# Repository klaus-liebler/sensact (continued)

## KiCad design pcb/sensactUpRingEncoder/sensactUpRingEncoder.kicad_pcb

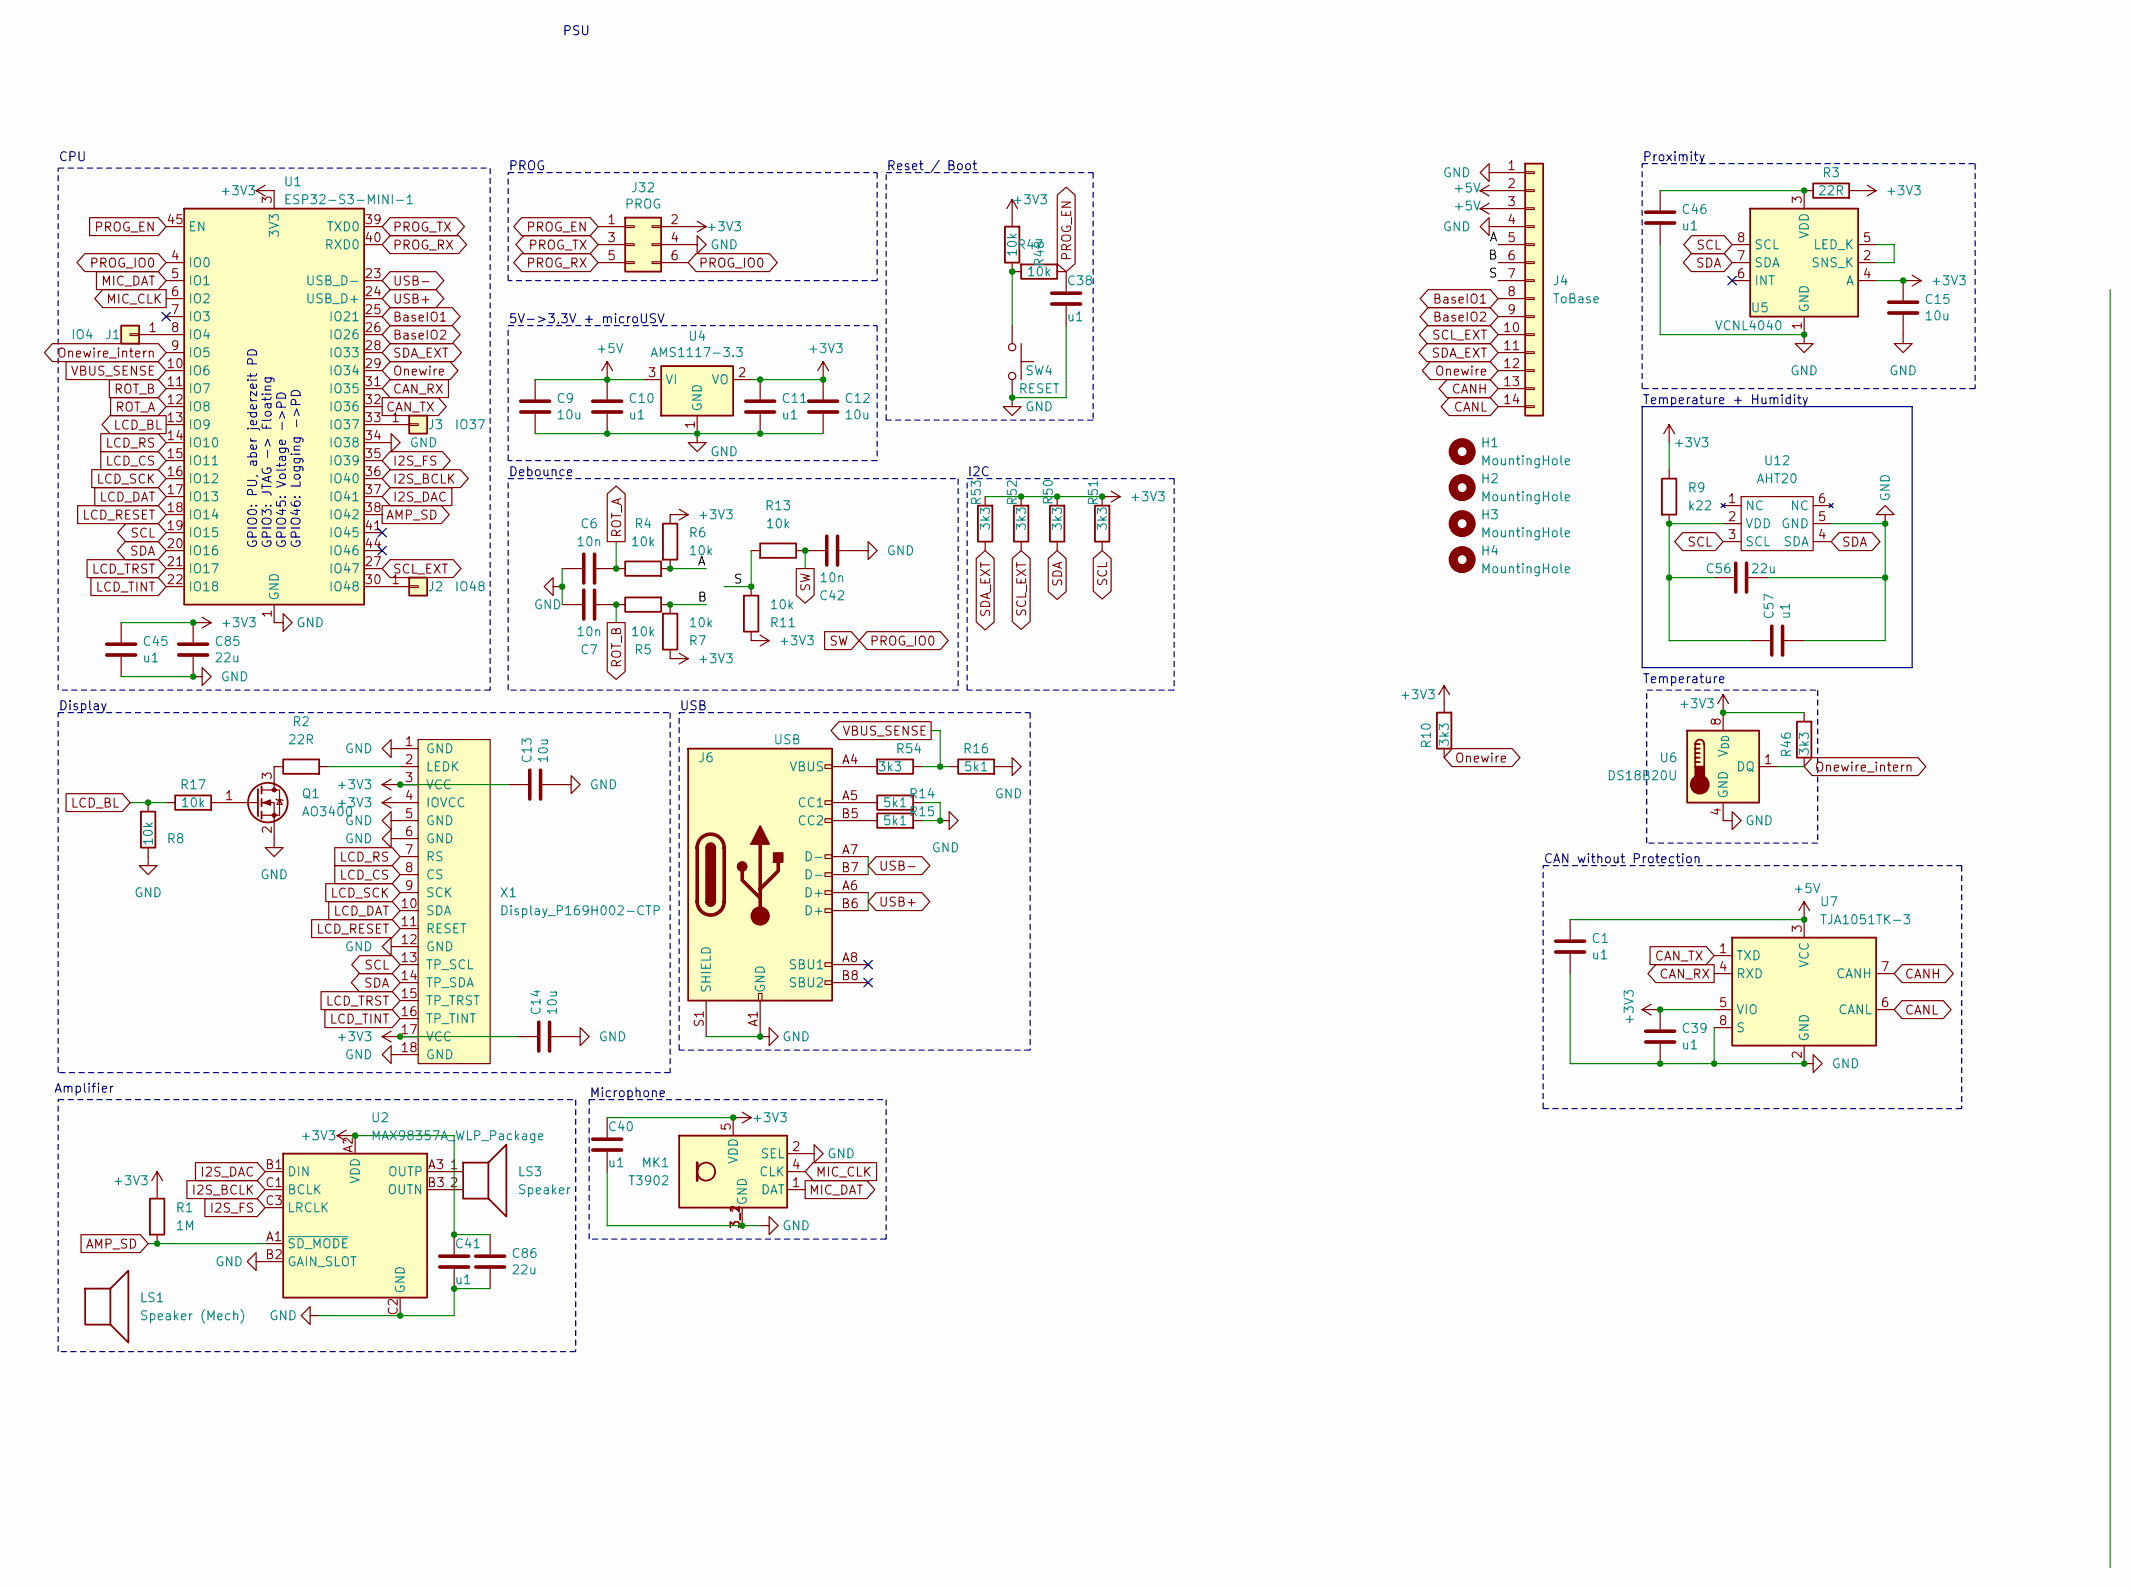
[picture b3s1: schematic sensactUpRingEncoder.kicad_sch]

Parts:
C1, C10, C11, C38, C39, C40, C41, C45, C46: u1; C_0201_0603Metric
C6, C7, C42: 10n; C_0201_0603Metric
C9, C12, C13, C14, C15: 10u; C_0402_1005Metric
C56, C85, C86: 22u; C_0603_1608Metric; MPN CL10A226MP8NUNE
C57: u1; C_0201_0603Metric; MPN GRM033R61A104KE15D
H1, H2, H3, H4: MountingHole; MountingHole_2.2mm_M2_DIN965
J1: IO4; TestPoint_THTPad_D1.0mm_Drill0.5mm
J2: IO48; TestPoint_THTPad_D1.5mm_Drill0.7mm
J3: IO37; TestPoint_THTPad_D1.5mm_Drill0.7mm
J4: ToBase; Hirose_FH12-14S-0.5SH_1x14-1MP_P0.50mm_Horizontal
J6: USB; USB_C_Receptacle_HRO_TYPE-C-31-M-12
J32: PROG; PinHeader_2x03_P1.27mm_Vertical_SMD
LS1: Speaker (Mech); SPEAKER_2415
LS3: Speaker; PinHeader_1x02_P1.27mm_Vertical
MK1: T3902; MIC_T3902
Q1: AO3400; SOT-23_smaller
R1: 1M; R_0805_2012Metric_Pad1.20x1.40mm_HandSolder
R2, R3: 22R; R_0805_2012Metric
R4, R5, R6, R7, R8, R11, R13, R17, R47, R48: 10k; R_0201_0603Metric
R9: k22; R_0805_2012Metric_Pad1.20x1.40mm_HandSolder; MPN 0402WGF2200TCE
R10, R46: 3k3; R_0402_1005Metric
R14, R15, R16: 5k1; R_0402_1005Metric
R50, R51, R52, R53, R54: 3k3; R_0402_1005Metric; MPN 0402WGF3301TCE
SW4: RESET; SW_Push_SPST_NO_4x3x2_handsolder
U1: ESP32-S3-MINI-1
U2: MAX98357A_WLP_Package; Maxim_WLP-9_1.595x1.415_Layout3x3_P0.4mm_Ball0.27mm_Pad0.25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
U4: AMS1117-3.3; SOT-223-3_TabPin2
U5: VCNL4040; VCNL4040_handsolder
U6: DS18B20U; MSOP-8_3x3mm_P0.65mm_handsolder
U7: TJA1051TK-3; HVSON-8-1EP_3x3mm_P0.65mm_EP1.6x2.4mm
U12: AHT20; AHT21; MPN AHT20
X1: Display_P169H002-CTP

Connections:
+3V3: C11.1, C12.1, C13.1, C14.1, C15.1, C39.1, C40.1, C41.1, C45.1, C85.1, C86.1, J32.2, MK1.5 (VDD), R1.1, R3.2, R6.1, R7.1, R9.1, R10.2, R11.1, R46.2, R47.2, R50.2, R51.2, R52.2, R53.2, U1.3 (3V3), U2.A2 (VDD), U4.2 (VO), U5.4 (A), U6.8 (V_{DD}), U7.5 (VIO), X1.3 (VCC), X1.4 (IOVCC), X1.17 (VCC)
+5V: C1.1, C9.1, C10.1, J4.2, J4.3, U4.3 (VI), U7.3 (VCC)
/A: J4.5, R4.2, R6.2
/B: J4.6, R5.2, R7.2
/S: J4.7, R11.2, R13.2
AMP_SD: R1.2, U1.38 (IO42), U2.A1 (~SD_MODE)
BaseIO1: J4.8, U1.25 (IO21)
BaseIO2: J4.9, U1.26 (IO26)
CANH: J4.13, U7.7 (CANH)
CANL: J4.14, U7.6 (CANL)
CAN_RX: U1.31 (IO35), U7.4 (RXD)
CAN_TX: U1.32 (IO36), U7.1 (TXD)
GND: C1.2, C6.1, C7.1, C9.2, C10.2, C11.2, C12.2, C13.2, C14.2, C15.2, C38.2, C39.2, C40.2, C41.2, C42.2, C45.2, C46.2, C56.2, C57.1, C85.2, C86.2, J4.1, J4.4, J6.A1 (GND), J6.A12 (GND), J6.B1 (GND), J6.B12 (GND), J6.S1 (SHIELD), J32.4, MK1.2 (SEL), MK1.3_1 (GND), MK1.3_2 (GND), Q1.2 (S), R8.1, R14.2, R15.2, R16.2, SW4.2, U1.1 (GND), U1.2 (GND), U1.34 (IO38), U1.42 (GND), U1.43 (GND), U1.46 (GND), U1.47 (GND), U1.48 (GND), U1.49 (GND), U1.50 (GND), U1.51 (GND), U1.52 (GND), U1.53 (GND), U1.54 (GND), U1.55 (GND), U1.56 (GND), U1.57 (GND), U1.58 (GND), U1.59 (GND), U1.60 (GND), U1.61 (GND), U1.62 (GND), U1.63 (GND), U1.64 (GND), U1.65 (GND), U2.B2 (GAIN_SLOT), U2.C2 (GND), U4.1 (GND), U5.1 (GND), U6.4 (GND), U7.2 (GND), U7.8 (S), U7.9 (GND), U12.5 (GND), X1.1 (GND), X1.5 (GND), X1.6 (GND), X1.12 (GND), X1.18 (GND)
I2S_BCLK: U1.36 (IO40), U2.C1 (BCLK)
I2S_DAC: U1.37 (IO41), U2.B1 (DIN)
I2S_FS: U1.35 (IO39), U2.C3 (LRCLK)
LCD_BL: R8.2, R17.1, U1.13 (IO9)
LCD_CS: U1.15 (IO11), X1.8 (CS)
LCD_DAT: U1.17 (IO13), X1.10 (SDA)
LCD_RESET: U1.18 (IO14), X1.11 (RESET)
LCD_RS: U1.14 (IO10), X1.7 (RS)
LCD_SCK: U1.16 (IO12), X1.9 (SCK)
LCD_TINT: U1.22 (IO18), X1.16 (TP_TINT)
LCD_TRST: U1.21 (IO17), X1.15 (TP_TRST)
MIC_CLK: MK1.4 (CLK), U1.6 (IO2)
MIC_DAT: MK1.1 (DAT), U1.5 (IO1)
unnamed: J1.1, U1.8 (IO4)
unnamed: J2.1, U1.30 (IO48)
unnamed: J3.1, U1.33 (IO37)
unnamed: J6.A5 (CC1), R14.1
unnamed: J6.B5 (CC2), R15.1
unnamed: J6.A4 (VBUS), J6.A9 (VBUS), J6.B4 (VBUS), J6.B9 (VBUS), R54.2
unnamed: Q1.3 (D), R2.1
unnamed: Q1.1 (G), R17.2
unnamed: R47.1, R48.2, SW4.1
unnamed: LS3.2, U2.B3 (OUTN)
unnamed: LS3.1, U2.A3 (OUTP)
unnamed: U5.2 (SNS_K), U5.5 (LED_K)
unnamed: C46.1, R3.1, U5.3 (VDD)
unnamed: C56.1, C57.2, R9.2, U12.2 (VDD)
unnamed: R2.2, X1.2 (LEDK)
Onewire: J4.12, R10.1, U1.29 (IO34)
Onewire_intern: R46.1, U1.9 (IO5), U6.1 (DQ)
PROG_EN: C38.1, J32.1, R48.1, U1.45 (EN)
PROG_IO0: C42.1, J32.6, R13.1, U1.4 (IO0)
PROG_RX: J32.5, U1.40 (RXD0)
PROG_TX: J32.3, U1.39 (TXD0)
ROT_A: C6.2, R4.1, U1.12 (IO8)
ROT_B: C7.2, R5.1, U1.11 (IO7)
SCL: R51.1, U1.19 (IO15), U5.8 (SCL), U12.3 (SCL), X1.13 (TP_SCL)
SCL_EXT: J4.10, R52.1, U1.27 (IO47)
SDA: R50.1, U1.20 (IO16), U5.7 (SDA), U12.4 (SDA), X1.14 (TP_SDA)
SDA_EXT: J4.11, R53.1, U1.28 (IO33)
USB+: J6.A6 (D+), J6.B6 (D+), U1.24 (USB_D+)
USB-: J6.A7 (D-), J6.B7 (D-), U1.23 (USB_D-)
VBUS_SENSE: R16.1, R54.1, U1.10 (IO6)

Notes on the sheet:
CAN without Protection
Temperature
Proximity
Reset / Boot
Temperature + Humidity
Amplifier
USB
5V->3,3V + microUSV
Debounce
Display
CPU
PSU
I2C
GPIO0: PU, aber jederzeit PD GPIO3: JTAG -> Floating GPIO45: Voltage ->PD GPIO46: Logging ->PD
Microphone
PROG

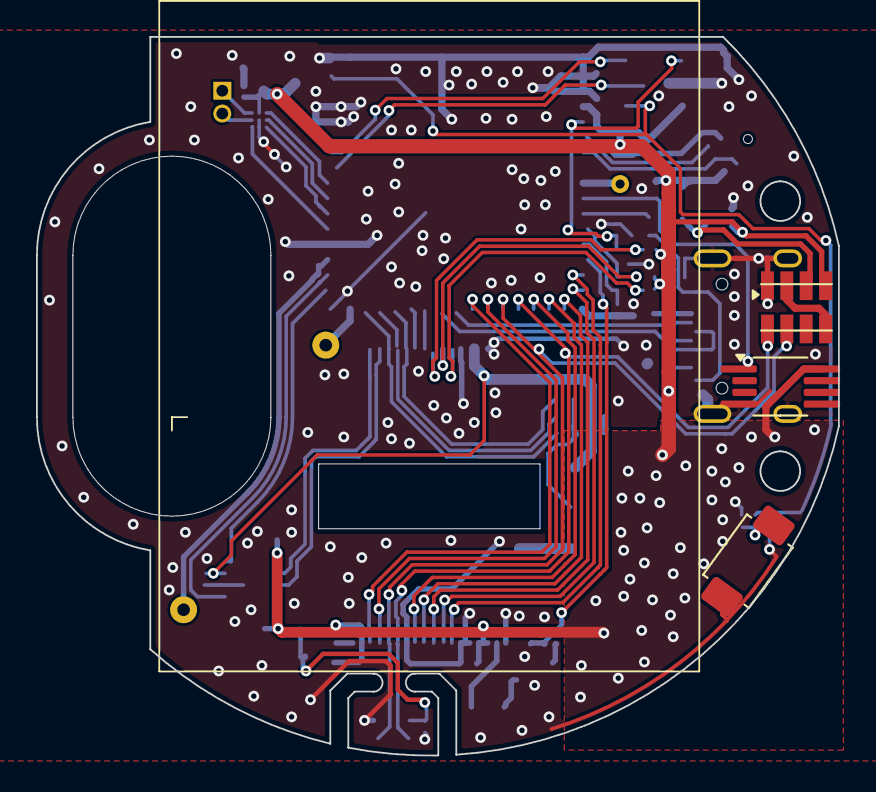
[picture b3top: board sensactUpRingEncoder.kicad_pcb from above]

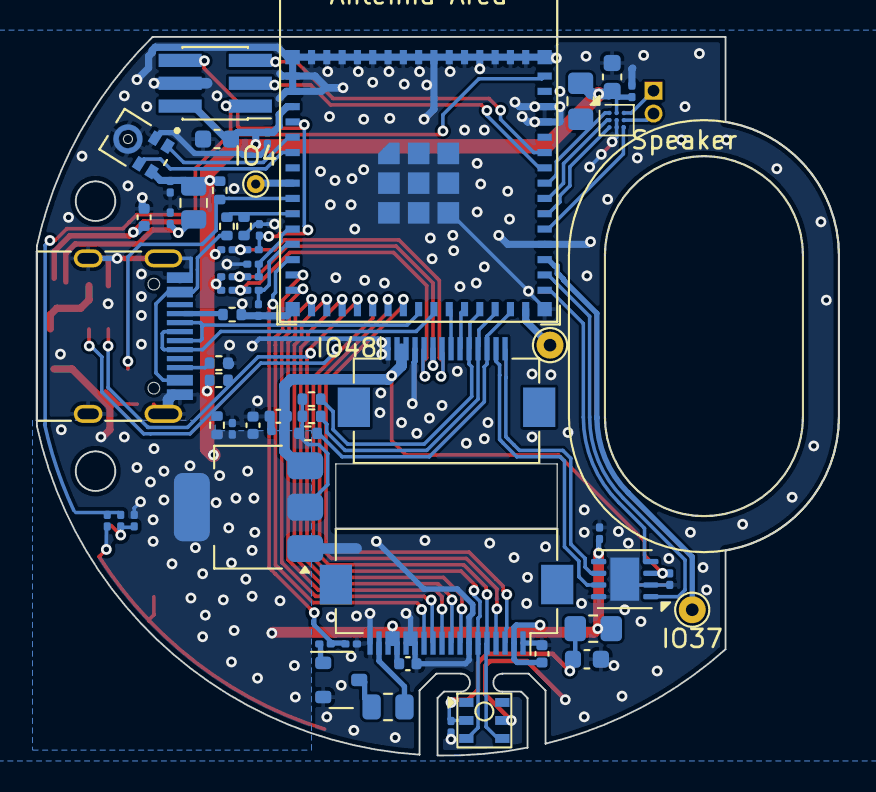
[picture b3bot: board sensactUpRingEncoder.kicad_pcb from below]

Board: 2 copper layers, 44.6 x 39.9 mm, 68 parts (61 on the bottom side), 56 nets.

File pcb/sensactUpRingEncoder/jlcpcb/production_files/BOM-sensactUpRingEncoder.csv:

Comment,Designator,Footprint,LCSC,Quantity
5k1,"R14,R15,R16",R_0402_1005Metric,C105872,3
10k,"R11,R13,R17,R4,R47,R48,R5,R6,R7,R8",R_0201_0603Metric,C106225,10
3k3,"R10,R46,R50,R51,R52,R53,R54",R_0402_1005Metric,C137992,7
USB,J6,USB_C_Receptacle_HRO_TYPE-C-31-M-12,C165948,1
22R,"R2,R3",R_0805_2012Metric,C17561,2
MAX98357A_WLP_Package,U2,Maxim_WLP-9_1.595x1.415_Layout3x3_P0.4mm_Ball0.27mm_Pad0.25mm_NSMD,C2682619,1
ToBase,J4,Hirose_FH12-14S-0.5SH_1x14-1MP_P0.50mm_Horizontal,C2856800,1
Display_P169H002-CTP,X1,Display_P169H002-CTP,C2856802,1
TJA1051TK-3,U7,HVSON-8-1EP_3x3mm_P0.65mm_EP1.6x2.4mm,C2875699,1
ESP32-S3-MINI-1,U1,ESP32-S3-MINI-1,C2913206,1
AHT20,U12,AHT21,C3012622,1
10u,"C12,C13,C14,C15,C9",C_0402_1005Metric,C315248,5
T3902,MK1,MIC_T3902,C3171752,1
AO3400,Q1,SOT-23_smaller,C347475,1
PROG,J32,PinHeader_2x03_P1.27mm_Vertical_SMD,C3975186,1
AMS1117-3.3,U4,SOT-223-3_TabPin2,C6186,1
u1,"C1,C10,C11,C38,C39,C40,C41,C45,C46,C57",C_0201_0603Metric,C76934,10
10n,"C42,C6,C7",C_0201_0603Metric,C76941,3
22u,"C56,C85,C86",C_0603_1608Metric,C86295,3
DS18B20U,U6,MSOP-8_3x3mm_P0.65mm_handsolder,,1
RESET,SW4,SW_Push_SPST_NO_4x3x2_handsolder,,1
VCNL4040,U5,VCNL4040_handsolder,,1

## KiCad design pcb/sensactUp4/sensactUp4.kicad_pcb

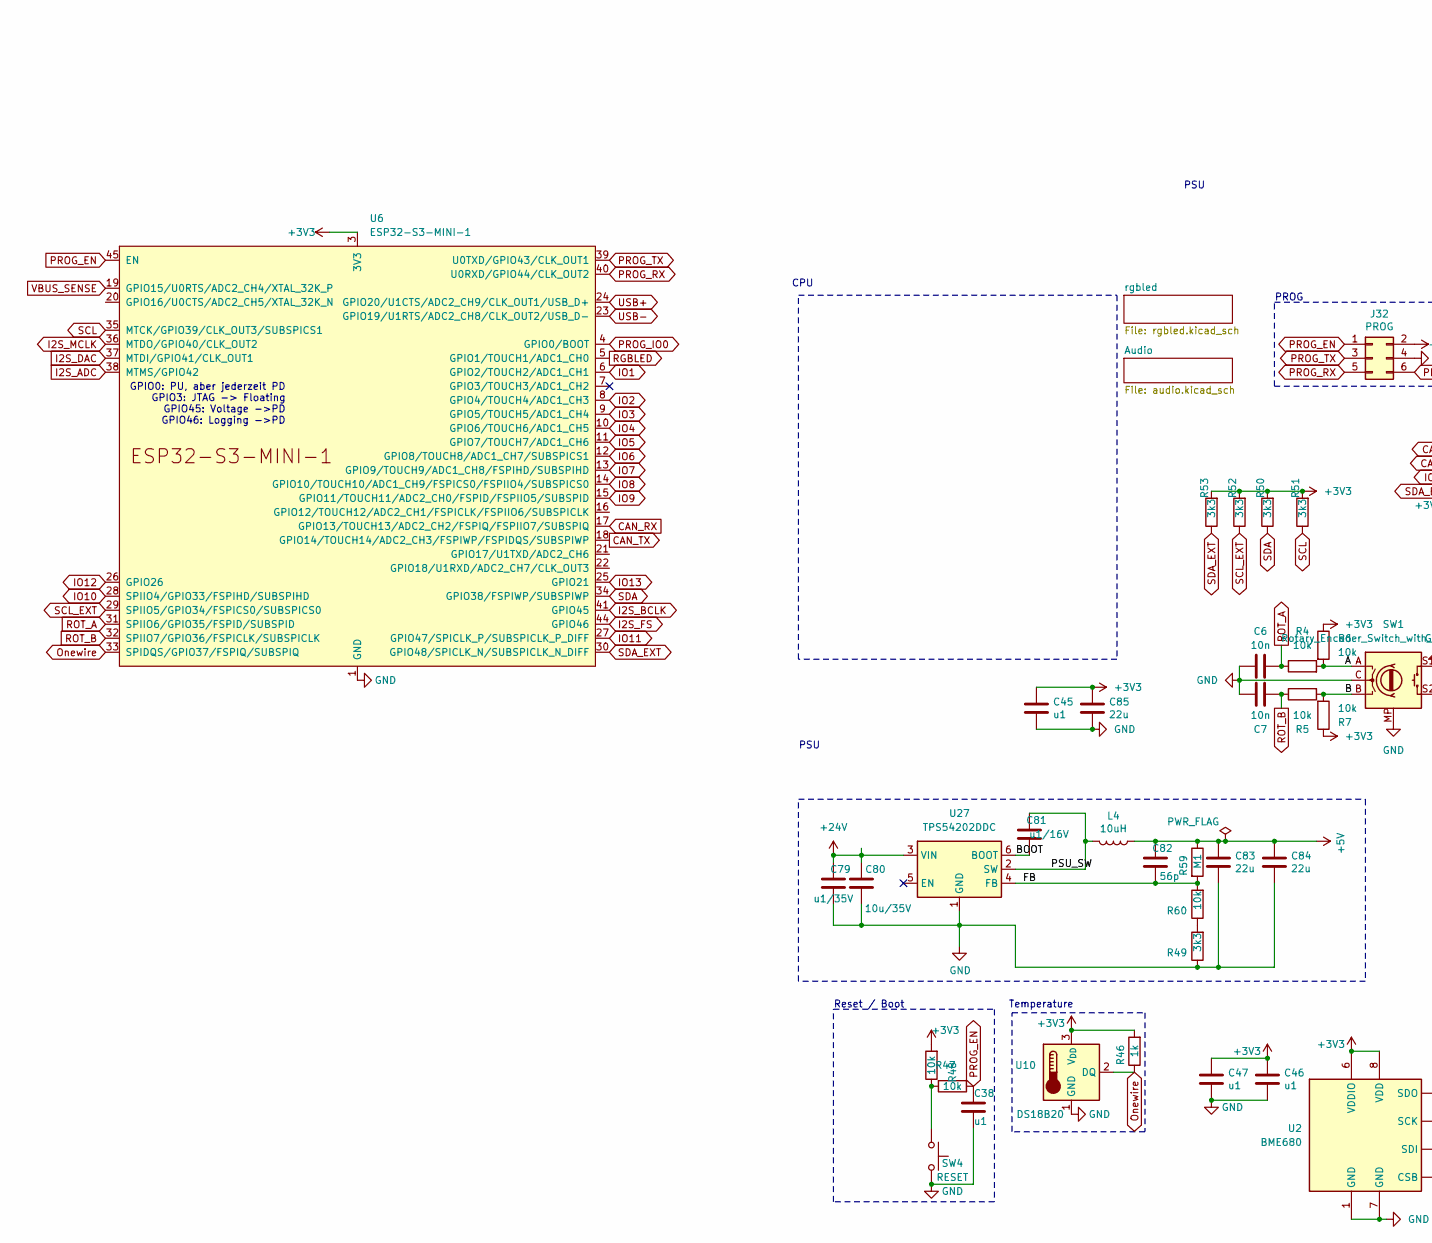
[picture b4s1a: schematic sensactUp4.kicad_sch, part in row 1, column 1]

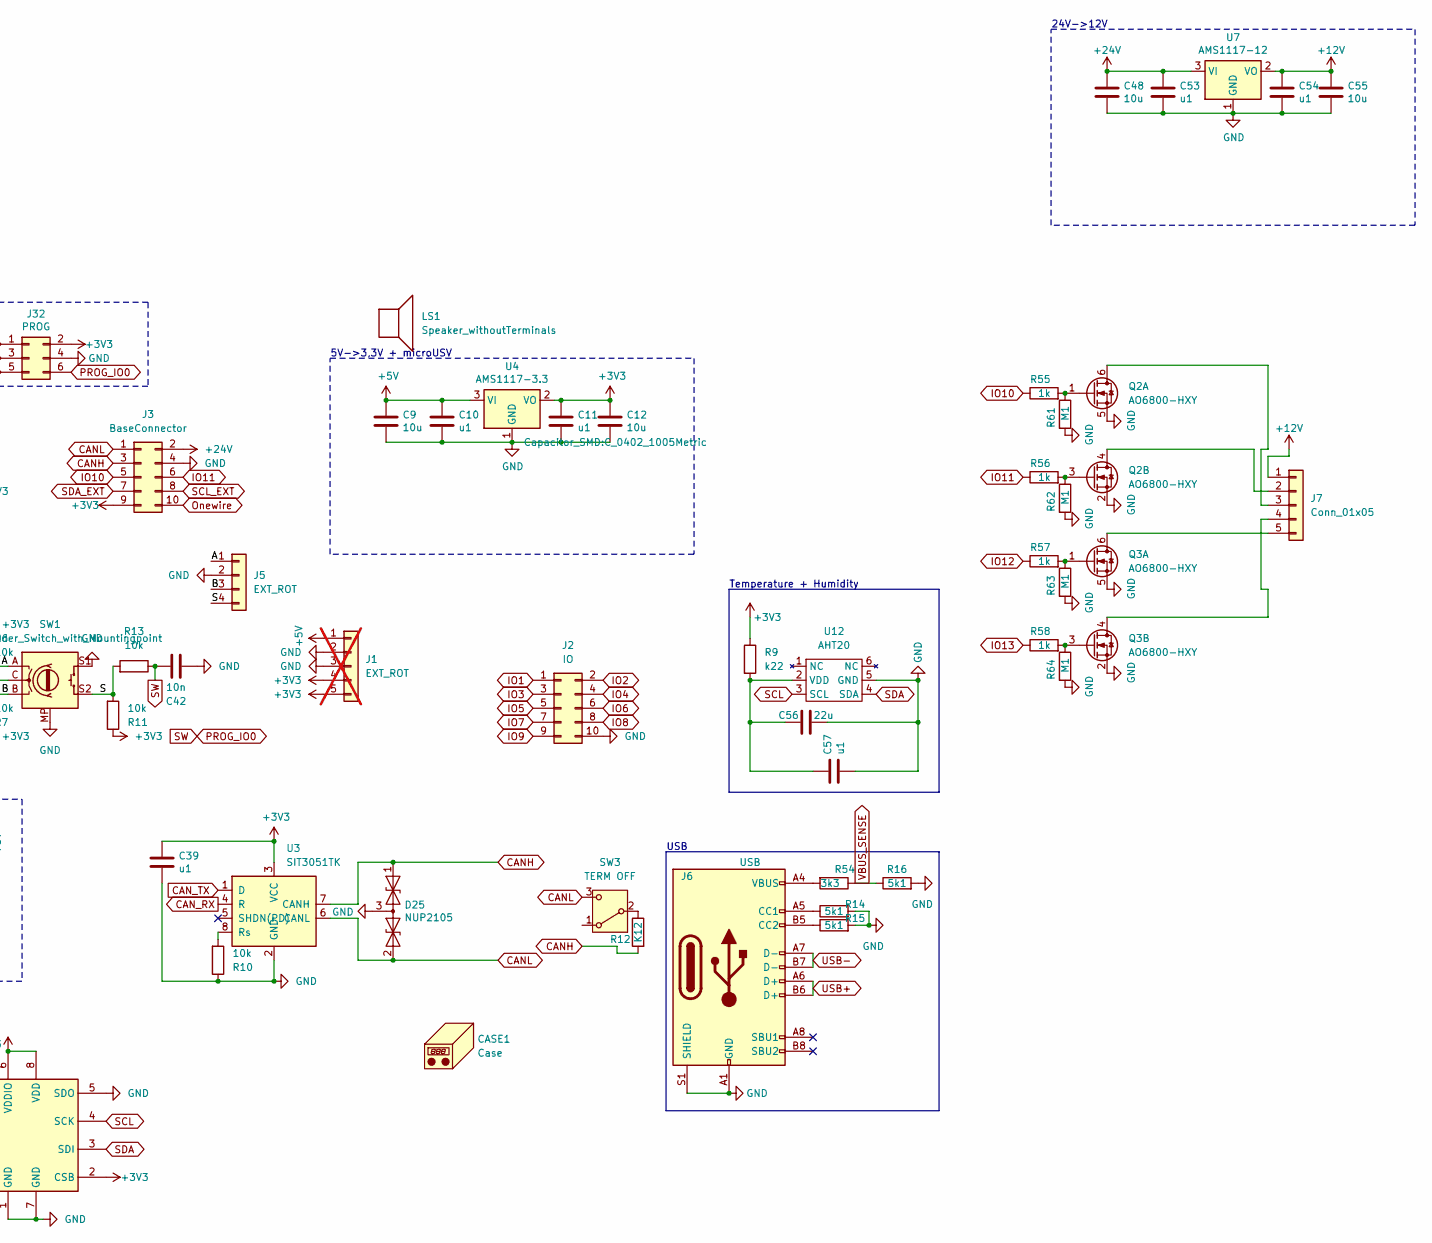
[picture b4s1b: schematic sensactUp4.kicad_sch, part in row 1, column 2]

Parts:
C6, C7, C42: 10n; C_0201_0603Metric
C9, C12: 10u; C_0402_1005Metric
C10, C11, C38, C39, C45, C46, C47: u1; C_0201_0603Metric
C48, C55: 10u; C_0805_2012Metric_Pad1.18x1.45mm_HandSolder
C53, C54: u1; C_0805_2012Metric_Pad1.18x1.45mm_HandSolder
C56, C83, C84, C85: 22u; C_0603_1608Metric; MPN CL10A226MP8NUNE
C57: u1; C_0201_0603Metric; MPN GRM033R61A104KE15D
C79: u1/35V; C_0603_1608Metric; MPN CC0603KRX7R9BB104
C80: 10u/35V; C_0805_2012Metric; MPN CGA0805X5R106K350MT
C81: u1/16V; C_0201_0603Metric; MPN CC0603KRX7R9BB104
C82: 56p; C_0201_0603Metric; MPN CC0402JRNPO9BN560
CASE1: Case; KiCad-Logo_5mm_SilkScreen
D25: NUP2105; SOT-23_Handsoldering; MPN NUP2105L
J1: EXT_ROT; PinHeader_1x05_P2.54mm_Vertical; not fitted
J2: IO; PinHeader_2x05_P2.54mm_Vertical
J3: BaseConnector; IDC-Header_2x05_P2.54mm_Vertical
J5: EXT_ROT; PhoenixContact_MCV_1,5_4-G-3.5_1x04_P3.50mm_Vertical
J6: USB; GT-USB-7051A
J7: Conn_01x05; PinHeader_1x05_P2.54mm_Vertical
J32: PROG; PinHeader_2x03_P2.54mm_Vertical
L4: 10uH; L_Abracon_ASPI-0630LR; MPN FXL0630-100-M
LS1: Speaker_withoutTerminals; SPEAKER_2415
Q2, Q3: AO6800-HXY; SOT-23-6
R4, R5, R6, R7, R10, R11, R13, R47, R48: 10k; R_0201_0603Metric
R9: k22; R_0402_1005Metric; MPN 0402WGF2200TCE
R12: K12; R_1206_3216Metric_Pad1.30x1.75mm_HandSolder; MPN 1206W4F1200T5E
R14, R15, R16: 5k1; R_0402_1005Metric
R46, R55, R56, R57, R58: 1k; R_0402_1005Metric
R49, R50, R51, R52, R53, R54: 3k3; R_0402_1005Metric; MPN 0402WGF3301TCE
R59, R61, R62, R63, R64: M1; R_0201_0603Metric; MPN 0201WMF1003TEE
R60: 10k; R_0201_0603Metric; MPN 0201WMF1002TEE
SW1: Rotary_Encoder_Switch_with_Mountingpoint; RotaryEncoder_Alps_EC11E-Switch_Vertical_H20mm
SW3: TERM OFF; Switch_SS12D00
SW4: RESET; SW_SPST_TL3342_smaller_handsolder
U2: BME680; Bosch_LGA-8_3x3mm_P0.8mm_ClockwisePinNumbering
U3: SIT3051TK; DFN-8-1EP_3x3mm_P0.65mm_EP1.55x2.4mm
U4: AMS1117-3.3; SOT-223-3_TabPin2
U6: ESP32-S3-MINI-1
U7: AMS1117-12; SOT-223-3_TabPin2_HANDSOLDER
U10: DS18B20; TO-92L_HandSolder
U12: AHT20; AHT21; MPN AHT20
U27: TPS54202DDC; SOT-23-6_Handsoldering; MPN TPS54202DDCR

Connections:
+3V3: C11.1, C12.1, C39.1, C45.1, C46.1, C47.1, C85.1, J1.4, J1.5, J3.9, J32.2, R6.1, R7.1, R9.1, R11.1, R46.2, R47.2, R50.2, R51.2, R52.2, R53.2, U2.2 (CSB), U2.6 (VDDIO), U2.8 (VDD), U3.3 (VCC), U4.2 (VO), U6.3 (3V3), U10.3 (V_{DD}); also elsewhere on the board
+5V: C9.1, C10.1, C82.2, C83.1, C84.1, J1.1, L4.1, R59.1, U4.3 (VI); also elsewhere on the board
+12V: C54.1, C55.1, J7.1, U7.2 (VO)
+24V: C48.1, C53.1, C79.2, C80.2, J3.2, U7.3 (VI), U27.3 (VIN)
/A: J5.1, R4.2, R6.2, SW1.A
/B: J5.3, R5.2, R7.2, SW1.B
/BOOT: C81.1, U27.6 (BOOT)
/FB: C82.1, R59.2, R60.2, U27.4 (FB)
/PSU_SW: C81.2, L4.2, U27.2 (SW)
/S: J5.4, R11.2, R13.2, SW1.S2
CANH: D25.1 (A1), J3.3, R12.2, U3.7 (CANH)
CANL: D25.2 (A2), J3.1, SW3.3 (C), U3.6 (CANL)
CAN_RX: U3.4 (R), U6.17 (GPIO13/TOUCH13/ADC2_CH2/FSPIQ/FSPIIO7/S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)
CAN_TX: U3.1 (D), U6.18 (GPIO14/TOUCH14/ADC2_CH3/FSPIWP/FSPIDQS/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)
GND: C6.1, C7.1, C9.2, C10.2, C11.2, C12.2, C38.2, C39.2, C42.2, C45.2, C46.2, C47.2, C48.2, C53.2, C54.2, C55.2, C56.2, C57.1, C79.1, C80.1, C83.2, C84.2, C85.2, D25.3 (common), J1.2, J1.3, J2.10, J3.4, J5.2, J6.A1 (GND), J6.A12 (GND), J6.B1 (GND), J6.B12 (GND), J6.S1 (SHIELD), J32.4, Q2.2 (S), Q2.5 (S), Q3.2 (S), Q3.5 (S), R10.1, R14.2, R15.2, R16.2, R49.1, R61.2, R62.2, R63.2, R64.2, SW1.C, SW1.MP, SW1.S1, SW4.2, U2.1 (GND), U2.5 (SDO), U2.7 (GND), U3.2 (GND), U3.9 (PAD), U4.1 (GND), U6.1 (GND), U6.2 (GND), U6.42 (GND), U6.43 (GND), U6.46 (GND), U6.47 (GND), U6.48 (GND), U6.49 (GND), U6.50 (GND), U6.51 (GND), U6.52 (GND), U6.53 (GND), U6.54 (GND), U6.55 (GND), U6.56 (GND), U6.57 (GND), U6.58 (GND), U6.59 (GND), U6.60 (GND), U6.61 (GND), U6.62 (GND), U6.63 (GND), U6.64 (GND), U6.65 (GND), U7.1 (GND), U10.1 (GND), U12.5 (GND), U27.1 (GND); also elsewhere on the board
I2S_ADC: U6.38 (MTMS/GPIO42); also elsewhere on the board
I2S_BCLK: U6.41 (GPIO45); also elsewhere on the board
I2S_DAC: U6.37 (MTDI/GPIO41/CLK_OUT1); also elsewhere on the board
I2S_FS: U6.44 (GPIO46); also elsewhere on the board
I2S_MCLK: U6.36 (MTDO/GPIO40/CLK_OUT2); also elsewhere on the board
IO1: J2.1, U6.6 (GPIO2/TOUCH2/ADC1_CH1)
IO2: J2.2, U6.8 (GPIO4/TOUCH4/ADC1_CH3)
IO3: J2.3, U6.9 (GPIO5/TOUCH5/ADC1_CH4)
IO4: J2.4, U6.10 (GPIO6/TOUCH6/ADC1_CH5)
IO5: J2.5, U6.11 (GPIO7/TOUCH7/ADC1_CH6)
IO6: J2.6, U6.12 (GPIO8/TOUCH8/ADC1_CH7/SUBSPICS1)
IO7: J2.7, U6.13 (GPIO9/TOUCH9/ADC1_CH8/FSPIHD/SUBSPIHD)
IO8: J2.8, U6.14 (GPIO10/TOUCH10/ADC1_CH9/FSPICS0/FSPIIO4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)
IO9: J2.9, U6.15 (GPIO11/TOUCH11/ADC2_CH0/FSPID/FSPIIO5/S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)
IO10: J3.5, R55.1, U6.28 (SPIIO4/GPIO33/FSPIHD/SUBSPIHD)
IO11: J3.6, R56.1, U6.27 (GPIO47/SPICLK_P/SUBSPICLK_P_DIFF)
IO12: R57.1, U6.26 (GPIO26)
IO13: R58.1, U6.25 (GPIO21)
unnamed: J6.A5 (CC1), R14.1
unnamed: J6.B5 (CC2), R15.1
unnamed: J6.A4 (VBUS), J6.A9 (VBUS), J6.B4 (VBUS), J6.B9 (VBUS), R54.2
unnamed: J7.2, Q2.4 (D)
unnamed: J7.3, Q2.6 (D)
unnamed: J7.4, Q3.4 (D)
unnamed: J7.5, Q3.6 (D)
unnamed: Q2.1 (G), R55.2, R61.1
unnamed: Q2.3 (G), R56.2, R62.1
unnamed: Q3.1 (G), R57.2, R63.1
unnamed: Q3.3 (G), R58.2, R64.1
unnamed: R47.1, R48.2, SW4.1
unnamed: R49.2, R60.1
unnamed: R12.1, SW3.2 (B)
unnamed: R10.2, U3.8 (Rs)
unnamed: C56.1, C57.2, R9.2, U12.2 (VDD)
Onewire: J3.10, R46.1, U6.33 (SPIDQS/GPIO37/FSPIQ/SUBSPIQ), U10.2 (DQ)
PROG_EN: C38.1, J32.1, R48.1, U6.45 (EN)
PROG_IO0: C42.1, J32.6, R13.1, U6.4 (GPIO0/BOOT)
PROG_RX: J32.5, U6.40 (U0RXD/GPIO44/CLK_OUT2)
PROG_TX: J32.3, U6.39 (U0TXD/GPIO43/CLK_OUT1)
RGBLED: U6.5 (GPIO1/TOUCH1/ADC1_CH0); also elsewhere on the board
ROT_A: C6.2, R4.1, U6.31 (SPIIO6/GPIO35/FSPID/SUBSPID)
ROT_B: C7.2, R5.1, U6.32 (SPIIO7/GPIO36/FSPICLK/SUBSPICLK)
SCL: R51.1, U2.4 (SCK), U6.35 (MTCK/GPIO39/CLK_OUT3/SUBSPICS1), U12.3 (SCL); also elsewhere on the board
SCL_EXT: J3.8, R52.1, U6.29 (SPIIO5/GPIO34/FSPICS0/SUBSPICS0)
SDA: R50.1, U2.3 (SDI), U6.34 (GPIO38/FSPIWP/SUBSPIWP), U12.4 (SDA); also elsewhere on the board
SDA_EXT: J3.7, R53.1, U6.30 (GPIO48/SPICLK_N/SUBSPICLK_N_DIFF)
USB+: J6.A6 (D+), J6.B6 (D+), U6.24 (GPIO20/U1CTS/ADC2_CH9/CLK_OUT1/USB_D+)
USB-: J6.A7 (D-), J6.B7 (D-), U6.23 (GPIO19/U1RTS/ADC2_CH8/CLK_OUT2/USB_D-)
VBUS_SENSE: R16.1, R54.1, U6.19 (GPIO15/U0RTS/ADC2_CH4/XTAL_32K_P)

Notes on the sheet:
Temperature
Reset / Boot
Temperature + Humidity
USB
5V->3,3V + microUSV
CPU
PSU
24V->12V
GPIO0: PU, aber jederzeit PD GPIO3: JTAG -> Floating GPIO45: Voltage ->PD GPIO46: Logging ->PD
PROG

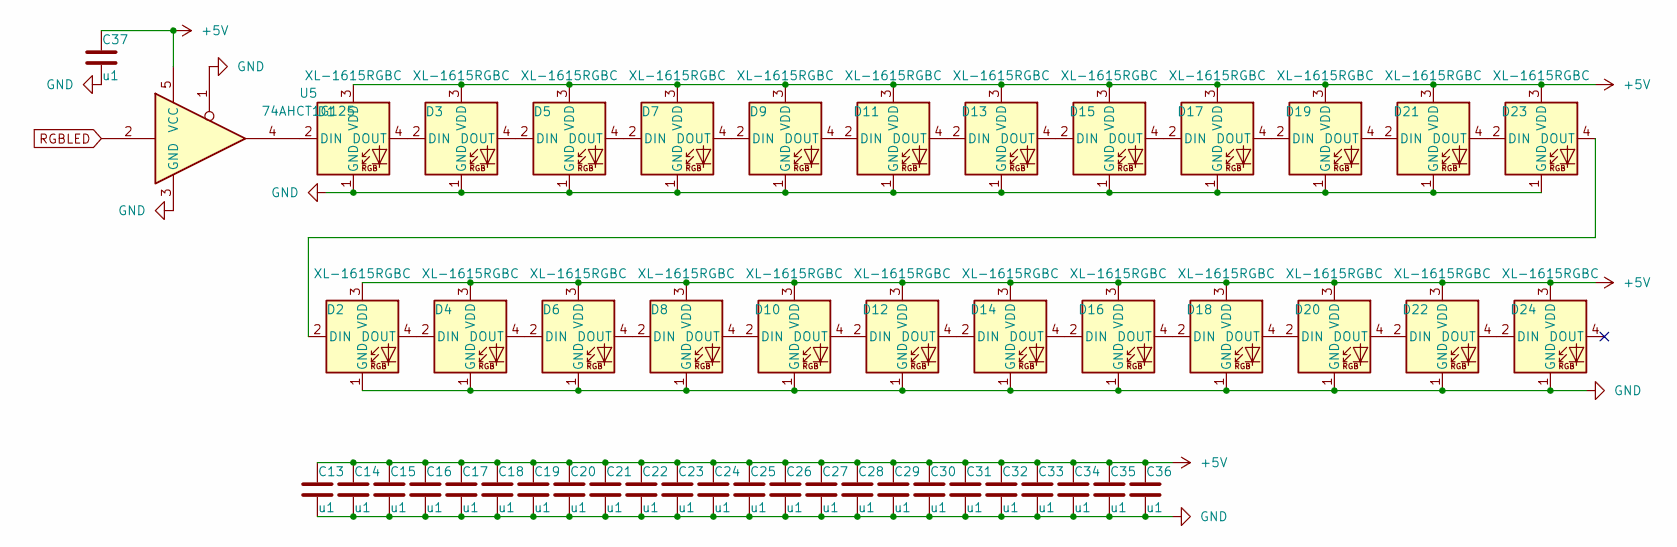
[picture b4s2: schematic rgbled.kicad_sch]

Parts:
C13, C14, C15, C16, C17, C18, C19, C20, C21, C22, C23, C24, C25, C26, C27, C28, C29, C30, C31, C32, C33, C34, C35, C36, C37: u1; C_0201_0603Metric
D1, D2, D3, D4, D5, D6, D7, D8, D9, D10, D11, D12, D13, D14, D15, D16, D17, D18, D19, D20, D21, D22, D23, D24: XL-1615RGBC; XL-1615
U5: 74AHCT1G125; SOT-23-5

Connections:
+5V: C13.1, C14.1, C15.1, C16.1, C17.1, C18.1, C19.1, C20.1, C21.1, C22.1, C23.1, C24.1, C25.1, C26.1, C27.1, C28.1, C29.1, C30.1, C31.1, C32.1, C33.1, C34.1, C35.1, C36.1, C37.1, D1.3 (VDD), D2.3 (VDD), D3.3 (VDD), D4.3 (VDD), D5.3 (VDD), D6.3 (VDD), D7.3 (VDD), D8.3 (VDD), D9.3 (VDD), D10.3 (VDD), D11.3 (VDD), D12.3 (VDD), D13.3 (VDD), D14.3 (VDD), D15.3 (VDD), D16.3 (VDD), D17.3 (VDD), D18.3 (VDD), D19.3 (VDD), D20.3 (VDD), D21.3 (VDD), D22.3 (VDD), D23.3 (VDD), D24.3 (VDD), U5.5 (VCC); also elsewhere on the board
GND: C13.2, C14.2, C15.2, C16.2, C17.2, C18.2, C19.2, C20.2, C21.2, C22.2, C23.2, C24.2, C25.2, C26.2, C27.2, C28.2, C29.2, C30.2, C31.2, C32.2, C33.2, C34.2, C35.2, C36.2, C37.2, D1.1 (GND), D2.1 (GND), D3.1 (GND), D4.1 (GND), D5.1 (GND), D6.1 (GND), D7.1 (GND), D8.1 (GND), D9.1 (GND), D10.1 (GND), D11.1 (GND), D12.1 (GND), D13.1 (GND), D14.1 (GND), D15.1 (GND), D16.1 (GND), D17.1 (GND), D18.1 (GND), D19.1 (GND), D20.1 (GND), D21.1 (GND), D22.1 (GND), D23.1 (GND), D24.1 (GND), U5.1, U5.3 (GND); also elsewhere on the board
unnamed: D1.2 (DIN), U5.4
unnamed: D1.4 (DOUT), D3.2 (DIN)
unnamed: D2.2 (DIN), D23.4 (DOUT)
unnamed: D2.4 (DOUT), D4.2 (DIN)
unnamed: D3.4 (DOUT), D5.2 (DIN)
unnamed: D4.4 (DOUT), D6.2 (DIN)
unnamed: D5.4 (DOUT), D7.2 (DIN)
unnamed: D6.4 (DOUT), D8.2 (DIN)
unnamed: D7.4 (DOUT), D9.2 (DIN)
unnamed: D8.4 (DOUT), D10.2 (DIN)
unnamed: D10.4 (DOUT), D12.2 (DIN)
unnamed: D9.4 (DOUT), D11.2 (DIN)
unnamed: D11.4 (DOUT), D13.2 (DIN)
unnamed: D12.4 (DOUT), D14.2 (DIN)
unnamed: D13.4 (DOUT), D15.2 (DIN)
unnamed: D14.4 (DOUT), D16.2 (DIN)
unnamed: D15.4 (DOUT), D17.2 (DIN)
unnamed: D16.4 (DOUT), D18.2 (DIN)
unnamed: D17.4 (DOUT), D19.2 (DIN)
unnamed: D18.4 (DOUT), D20.2 (DIN)
unnamed: D19.4 (DOUT), D21.2 (DIN)
unnamed: D20.4 (DOUT), D22.2 (DIN)
unnamed: D21.4 (DOUT), D23.2 (DIN)
unnamed: D22.4 (DOUT), D24.2 (DIN)
RGBLED: U5.2; also elsewhere on the board

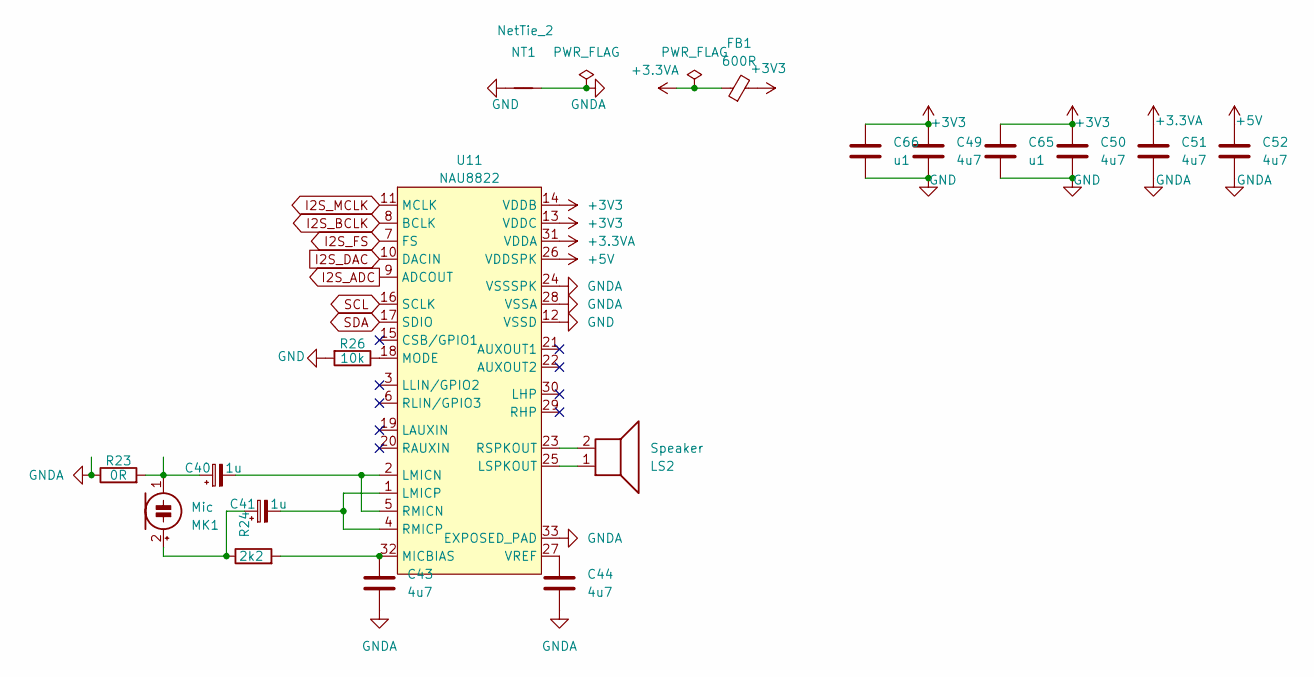
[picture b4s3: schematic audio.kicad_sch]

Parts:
C40, C41: 1u; CP_EIA-3216-10_Kemet-I; MPN TAJA105K016RNJ
C43, C44, C49, C50, C51, C52: 4u7; C_0402_1005Metric; MPN CL05A475MP5NRNC
C65, C66: u1; C_0201_0603Metric; MPN GRM033R61A104KE15D
FB1: 600R; L_0603_1608Metric; MPN BLM18AG601SN1D
LS2: Speaker; PinHeader_1x02_P1.27mm_Vertical
MK1: Mic; Microphone_6mm; MPN GMI6050P-64DB
NT1: NetTie_2; NetTie-2_SMD_Pad0.5mm
R23: 0R; R_0805_2012Metric_Pad1.20x1.40mm_HandSolder; MPN 0805W8F0000T5E
R24: 2k2; R_0402_1005Metric; MPN 0402WGF2201TCE
R26: 10k; R_0201_0603Metric; MPN 0201WMF1002TEE
U11: NAU8822; QFN-32-1EP_5x5mm_P0.5mm_EP3.6x3.6mm_ThermalVias; MPN NAU88C22YG

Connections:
+3.3VA: C51.1, FB1.1, U11.31 (VDDA)
+3V3: C49.1, C50.1, C65.1, C66.1, FB1.2, U11.13 (VDDC), U11.14 (VDDB); also elsewhere on the board
+5V: C52.1, U11.26 (VDDSPK); also elsewhere on the board
GND: C49.2, C50.2, C65.2, C66.2, NT1.1, R26.2, U11.12 (VSSD); also elsewhere on the board
GNDA: C43.2, C44.2, C51.2, C52.2, NT1.2, R23.1, U11.24 (VSSSPK), U11.28 (VSSA), U11.33 (EXPOSED_PAD)
I2S_ADC: U11.9 (ADCOUT); also elsewhere on the board
I2S_BCLK: U11.8 (BCLK); also elsewhere on the board
I2S_DAC: U11.10 (DACIN); also elsewhere on the board
I2S_FS: U11.7 (FS); also elsewhere on the board
I2S_MCLK: U11.11 (MCLK); also elsewhere on the board
unnamed: C41.1, MK1.2 (+), R24.1
unnamed: C40.1, MK1.1 (-), R23.2
unnamed: C40.2, U11.2 (LMICN), U11.5 (RMICN)
unnamed: C41.2, U11.1 (LMICP), U11.4 (RMICP)
unnamed: LS2.1, U11.25 (LSPKOUT)
unnamed: C43.1, R24.2, U11.32 (MICBIAS)
unnamed: R26.1, U11.18 (MODE)
unnamed: LS2.2, U11.23 (RSPKOUT)
unnamed: C44.1, U11.27 (VREF)
SCL: U11.16 (SCLK); also elsewhere on the board
SDA: U11.17 (SDIO); also elsewhere on the board
